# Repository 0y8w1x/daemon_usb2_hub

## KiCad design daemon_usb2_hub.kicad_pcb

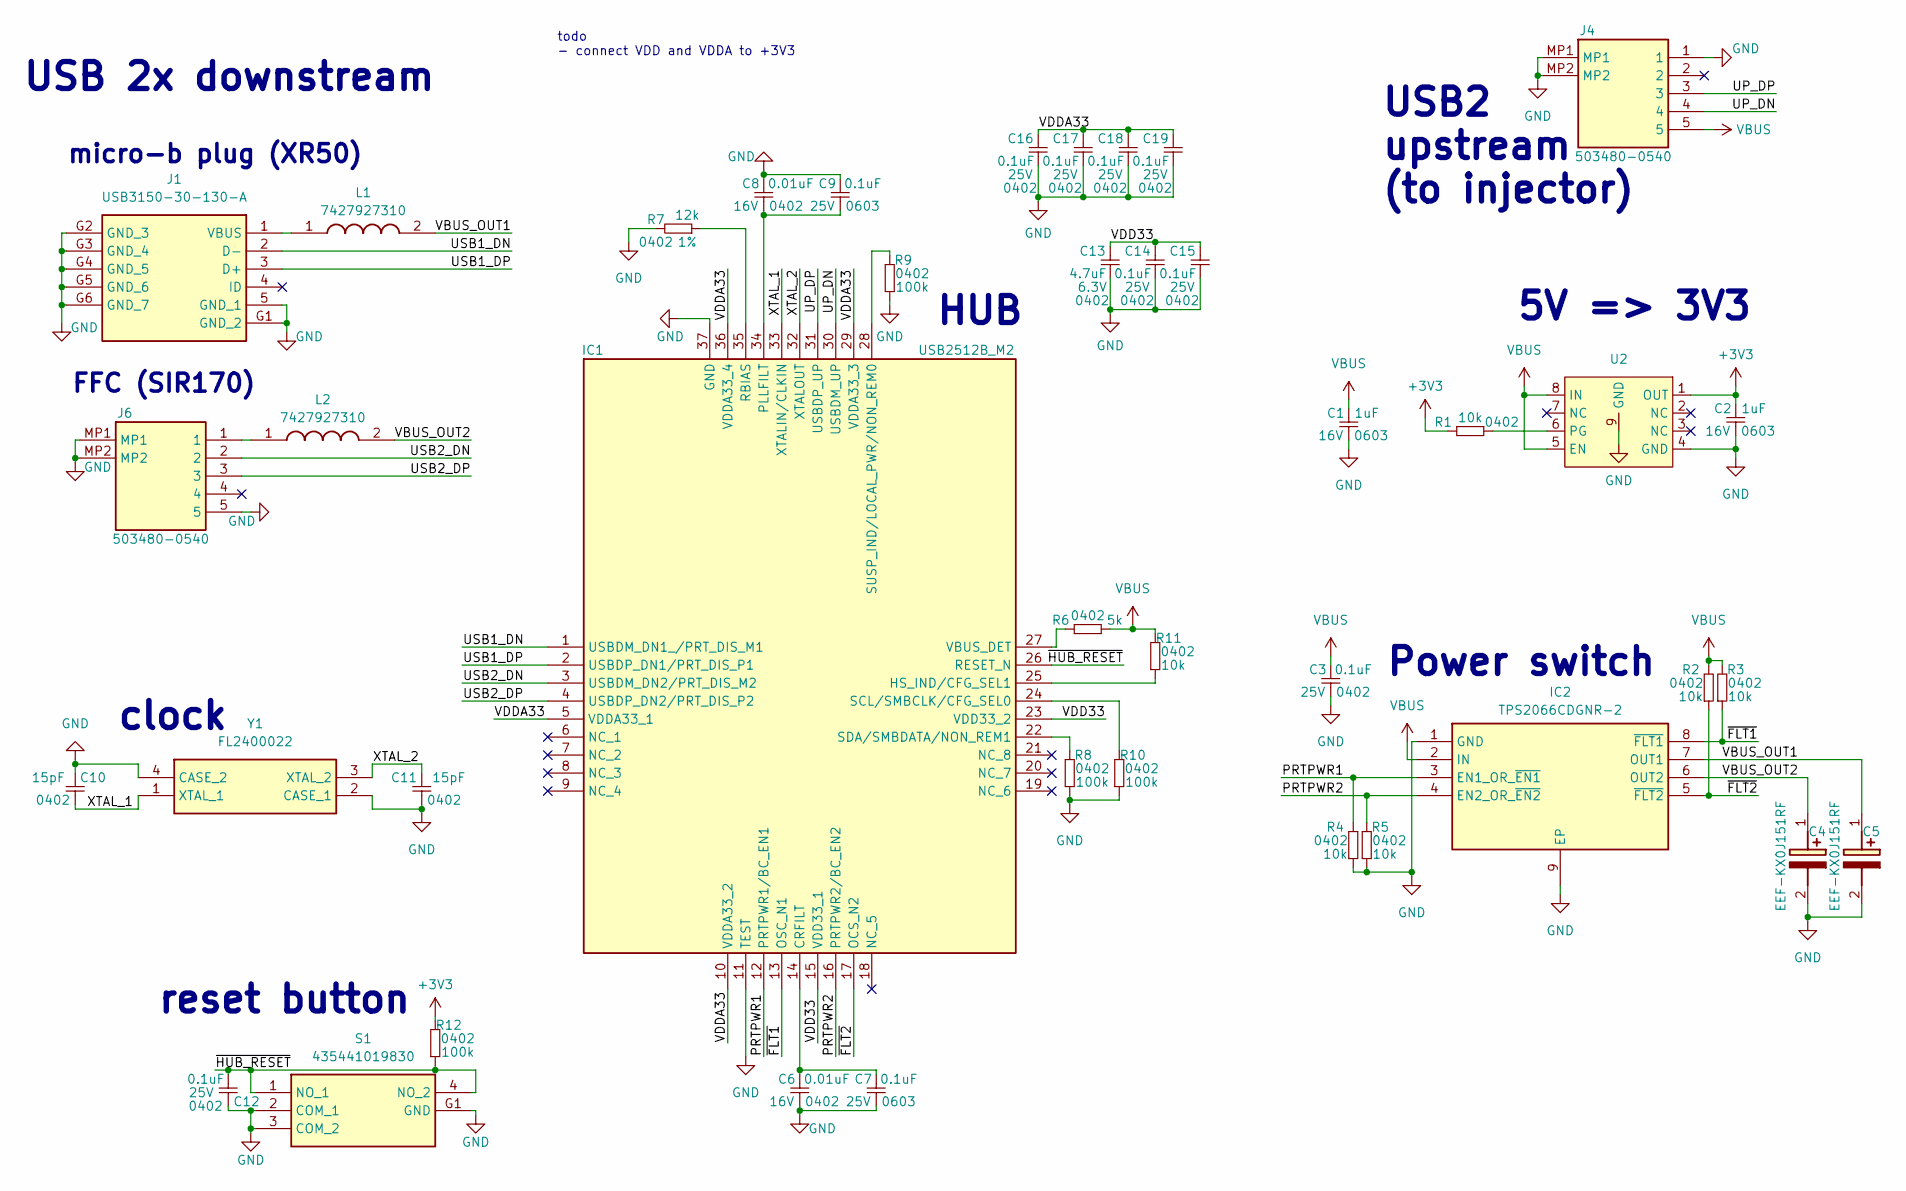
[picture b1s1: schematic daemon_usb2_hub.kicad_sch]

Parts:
C1, C2: 1uF; 0603_cap; Voltage 16V
C3, C12, C14, C15, C16, C17, C18, C19: 0.1uF; 0402_cap; Voltage 25V
C4, C5: EEF-KX0J151RF; EEFKX0G181RF; Manufacturer_Part_Number EEF-KX0J151RF; Mouser Part Number 667-EEF-KX0J151RF
C6, C8: 0.01uF; 0402_cap; Voltage 16V
C7, C9: 0.1uF; 0603_cap; Voltage 25V
C10, C11: 15pF; 0402_cap; Voltage 50V
C13: 4.7uF; 0402_cap; Voltage 6.3V
IC1: USB2512B_M2; QFN50P600X600X100-37N-D; Manufacturer_Part_Number USB2512B/M2; Mouser Part Number 579-USB2512B/M2
IC2: TPS2066CDGNR-2; SOP65P490X110-9N; Manufacturer_Part_Number TPS2066CDGNR-2; Mouser Part Number 595-TPS2066CDGNR-2
J1: USB3150-30-130-A; USB315030130A; Manufacturer_Part_Number USB3150-30-130-A; Mouser Part Number 640-USB3150-30-130-A
J4, J6: 503480-0540; 5034800540; Manufacturer_Part_Number 503480-0540; Mouser Part Number 538-503480-0540
L1, L2: 7427927310; 0402; Manufacturer_Part_Number 7427927310; Mouser Part Number 710-7427927310
R1, R2, R3, R4, R5, R11: 10k; 0402_res
R6: 5k; 0402_res
R7: 12k; 0402_res
R8, R9, R10, R12: 100k; 0402_res
S1: 435441019830; Manufacturer_Part_Number 435441019830; Mouser Part Number 710-435441019830
U2: TPS74633PQWDRBRQ1
Y1: FL2400022; Manufacturer_Part_Number FL2400022; Mouser Part Number 729-FL2400022

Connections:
+3V3: C2.2, R1.1, R12.2, U2.1 (OUT)
/PRTPWR1: IC1.12 (PRTPWR1/BC_EN1), IC2.3 (EN1_OR_~EN1), R4.2
/PRTPWR2: IC1.16 (PRTPWR2/BC_EN2), IC2.4 (EN2_OR_~EN2), R5.2
/UP_DN: IC1.30 (USBDM_UP), J4.4
/UP_DP: IC1.31 (USBDP_UP), J4.3
/USB1_DN: IC1.1 (USBDM_DN1_/PRT_DIS_M1), J1.2 (D-)
/USB1_DP: IC1.2 (USBDP_DN1/PRT_DIS_P1), J1.3 (D+)
/USB2_DN: IC1.3 (USBDM_DN2/PRT_DIS_M2), J6.2
/USB2_DP: IC1.4 (USBDP_DN2/PRT_DIS_P2), J6.3
/VBUS_OUT1: C5.1 (+), IC2.7 (OUT1), L1.2
/VBUS_OUT2: C4.1 (+), IC2.6 (OUT2), L2.2
/VDD33: C13.2, C14.2, C15.2, IC1.15 (VDD33_1), IC1.23 (VDD33_2)
/VDDA33: C16.2, C17.2, C18.2, C19.2, IC1.5 (VDDA33_1), IC1.10 (VDDA33_2), IC1.29 (VDDA33_3), IC1.36 (VDDA33_4)
/XTAL_1: C10.1, IC1.33 (XTALIN/CLKIN), Y1.1 (XTAL_1)
/XTAL_2: C11.2, IC1.32 (XTALOUT), Y1.3 (XTAL_2)
/~FLT1: IC1.13 (OSC_N1), IC2.8 (~FLT1), R3.1
/~FLT2: IC1.17 (OCS_N2), IC2.5 (~FLT2), R2.1
/~HUB_RESET: C12.2, IC1.26 (RESET_N), R12.1, S1.1 (NO_1), S1.4 (NO_2)
GND: C1.1, C2.1, C3.1, C4.2 (-), C5.2 (-), C6.1, C7.1, C8.2, C9.2, C10.2, C11.1, C12.1, C13.1, C14.1, C15.1, C16.1, C17.1, C18.1, C19.1, IC1.11 (TEST), IC1.37 (GND), IC2.1 (GND), IC2.9 (EP), J1.5 (GND_1), J1.G1 (GND_2), J1.G2 (GND_3), J1.G3 (GND_4), J1.G4 (GND_5), J1.G5 (GND_6), J1.G6 (GND_7), J4.1, J4.MP1, J4.MP2, J6.5, J6.MP1, J6.MP2, R4.1, R5.1, R7.2, R8.1, R9.1, R10.1, S1.2 (COM_1), S1.3 (COM_2), S1.G1 (GND), U2.4 (GND), U2.9 (GND), Y1.2 (CASE_1), Y1.4 (CASE_2)
unnamed: C6.2, C7.2, IC1.14 (CRFILT)
unnamed: IC1.25 (HS_IND/CFG_SEL1), R11.1
unnamed: C8.1, C9.1, IC1.34 (PLLFILT)
unnamed: IC1.35 (RBIAS), R7.1
unnamed: IC1.24 (SCL/SMBCLK/CFG_SEL0), R10.2
unnamed: IC1.22 (SDA/SMBDATA/NON_REM1), R8.2
unnamed: IC1.28 (SUSP_IND/LOCAL_PWR/NON_REM0), R9.2
unnamed: IC1.27 (VBUS_DET), R6.2
unnamed: J1.1 (VBUS), L1.1
unnamed: J6.1, L2.1
unnamed: R1.2, U2.6 (PG)
VBUS: C1.2, C3.2, IC2.2 (IN), J4.5, R2.2, R3.2, R6.1, R11.2, U2.5 (EN), U2.8 (IN)

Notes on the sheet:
clock
FFC (SIR170)
micro-b plug (XR50)
reset button
Power switch
HUB
USB 2x downstream
5V => 3V3
todo - connect VDD and VDDA to +3V3
USB2 upstream (to injector)

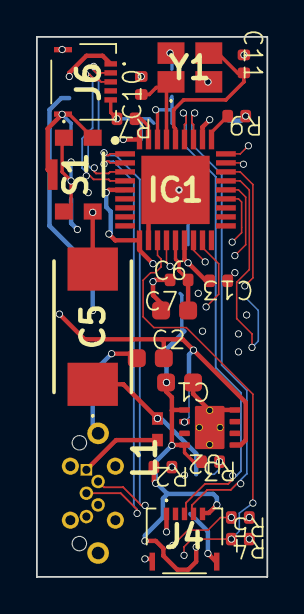
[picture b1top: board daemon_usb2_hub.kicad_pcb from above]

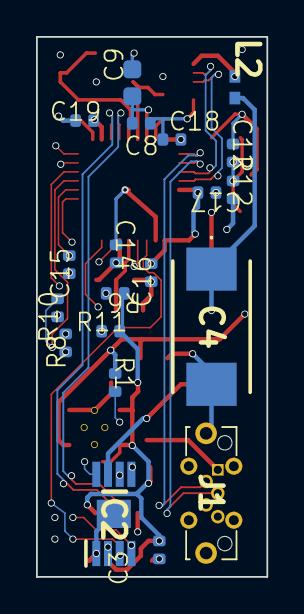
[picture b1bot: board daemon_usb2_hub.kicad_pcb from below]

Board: 4 copper layers, 12.8 x 30.0 mm, 41 parts (20 on the bottom side), 31 nets.

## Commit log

2024-04-20 init
2024-07-27 changed files
